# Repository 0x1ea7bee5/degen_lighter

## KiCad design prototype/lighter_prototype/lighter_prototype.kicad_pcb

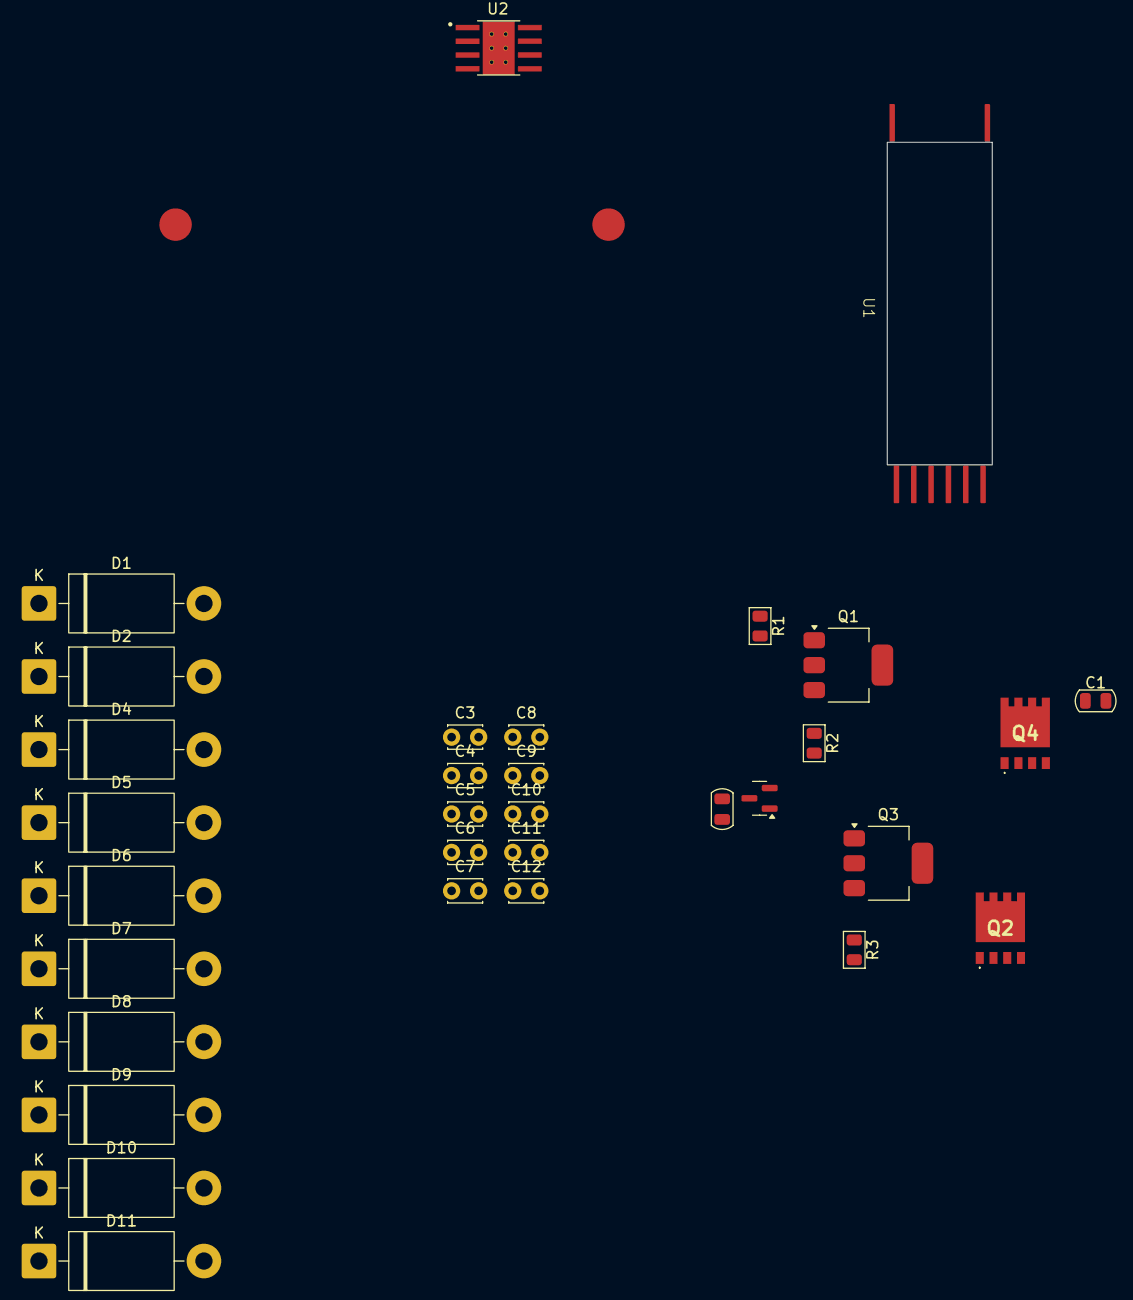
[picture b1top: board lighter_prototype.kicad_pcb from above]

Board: 2 copper layers, 33 parts (0 on the bottom side), 19 nets, no tracks yet.

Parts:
C1, C2: C_0805; C_0805_2012Metric
C3, C4, C5, C6, C7, C8, C9, C10, C11, C12: Capacitor_NP; C_Disc_D3.0mm_W2.0mm_P2.50mm
D1, D2, D4, D5, D6, D7, D8, D9, D10, D11: 1N5400; D_DO-201AD_P15.24mm_Horizontal
D3: BZX84Cxx; SOT-23
Q1, Q3: BSP89; SOT-223-3_TabPin2
Q2, Q4: RS6R035BHTB1
R1, R2, R3: R_0805; R_0805_2012Metric
U1: coilcraft_FL32095LD
U2: TPS54531DDAR; CONV_TPS54531DDAR
U3: spark_gat

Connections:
/mazzilli/power_fet_1_out: C1.2, Q2.5 (D_1), Q2.6 (D_2), Q2.7 (D_3), Q2.8 (D_4), Q2.9 (D_5), Q3.2 (D), U1.2 (PR1)
/mazzilli/power_fet_2_out: C1.1, Q1.2 (D), Q4.5 (D_1), Q4.6 (D_2), Q4.7 (D_3), Q4.8 (D_4), Q4.9 (D_5), U1.4 (PR2)
/mazzilli/signal_fet_1_source: Q1.3 (S), Q2.4 (G), R2.1
/mazzilli/signal_fet_2_source: Q3.3 (S), Q4.4 (G), R3.1
/mazzilli/source_resistor: C2.1, D3.3 (K), Q1.1 (G), Q3.1 (G), R1.2
/mazzilli/v_mazzilli_n: C3.1, U1.7 (S1)
/mazzilli/v_mazzilli_p: C4.2, D1.2 (A), U1.6 (S2)
GND: C2.2, D3.1 (A), Q2.1 (S_1), Q2.2 (S_2), Q2.3 (S_3), Q4.1 (S_1), Q4.2 (S_2), Q4.3 (S_3), R2.2, R3.2
unnamed: C3.2, C5.1, D1.1 (K), D2.2 (A)
unnamed: C4.1, C6.2, D2.1 (K), D4.2 (A)
unnamed: C5.2, C7.1, D4.1 (K), D5.2 (A)
unnamed: C6.1, C8.2, D5.1 (K), D6.2 (A)
unnamed: C7.2, C9.1, D6.1 (K), D7.2 (A)
unnamed: C8.1, C10.2, D7.1 (K), D8.2 (A)
unnamed: C9.2, C11.1, D8.1 (K), D9.2 (A)
unnamed: C10.1, C12.2, D9.1 (K), D10.2 (A)
unnamed: C11.2, D10.1 (K), D11.2 (A), U3.2 (term)
unnamed: C12.1, D11.1 (K), U3.1 (term)
V_HV: R1.1, U1.3 (PM)
